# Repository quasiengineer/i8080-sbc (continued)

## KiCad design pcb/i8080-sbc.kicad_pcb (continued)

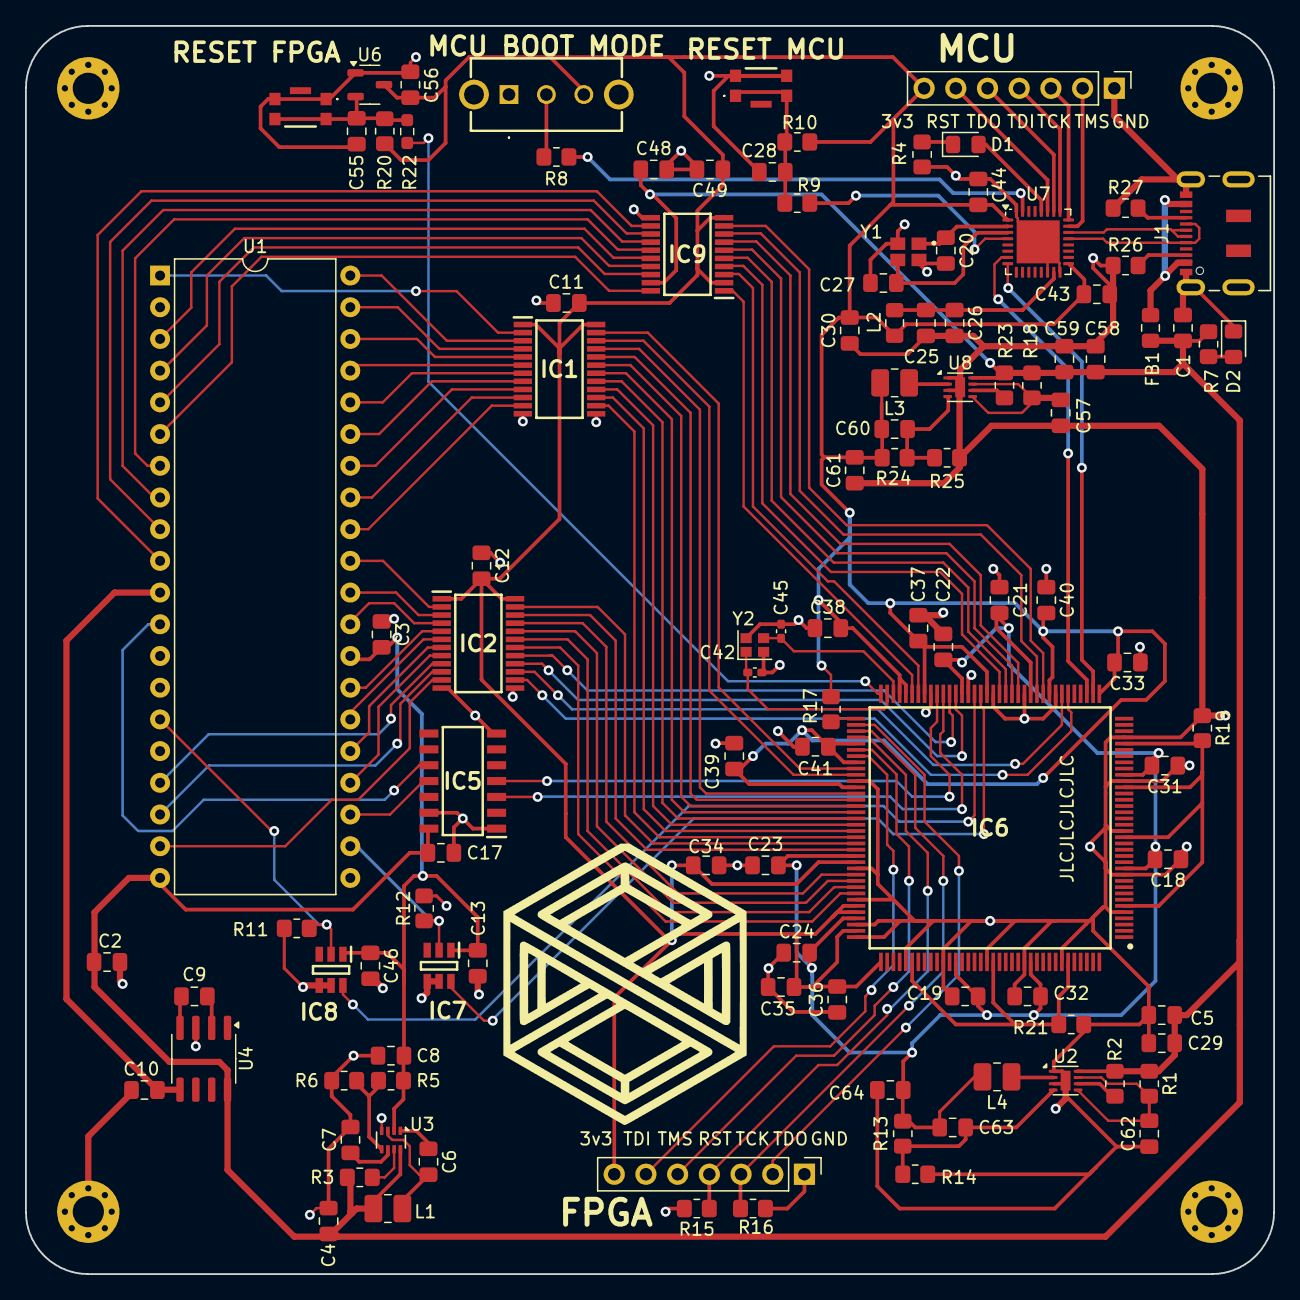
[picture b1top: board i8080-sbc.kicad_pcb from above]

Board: 2 copper layers, 100.0 x 100.0 mm, 115 parts (0 on the bottom side), 119 nets.

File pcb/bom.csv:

"Reference","Value","Footprint","Mouser Part Number","Qty"
"C1,C7,C25,C57,C62","1u","Capacitor_SMD:C_0805_2012Metric_Pad1.18x1.45mm_HandSolder","187-CL21B105KAFNNNG","5"
"C2,C3,C6,C11,C12,C13,C17,C18,C19,C21,C22,C23,C24,C26,C28,C29,C31,C32,C33,C34,C35,C36,C37,C38,C39,C40,C41,C43,C44,C46,C48,C49,C56,C58","100n","Capacitor_SMD:C_0805_2012Metric_Pad1.18x1.45mm_HandSolder","187-CL21B104KBCNNND","34"
"C4,C30","4u7,4u7, low-ESR","Capacitor_SMD:C_0805_2012Metric_Pad1.18x1.45mm_HandSolder","187-CL21A475KAQNNNE","2"
"C5,C59,C61,C64","22u","Capacitor_SMD:C_0805_2012Metric_Pad1.18x1.45mm_HandSolder","187-CL21A226MAYNNNE","4"
"C8,C9,C10,C55","10u,10u, low-ESR","Capacitor_SMD:C_0805_2012Metric_Pad1.18x1.45mm_HandSolder","187-CL21A106KAYNNNF","4"
"C20,C27","10p","Capacitor_SMD:C_0805_2012Metric_Pad1.18x1.45mm_HandSolder","710-885012007051","2"
"C42,C45","10p","Capacitor_SMD:C_0402_1005Metric_Pad0.74x0.62mm_HandSolder","603-CC402JRNPO8BN100","2"
"C60","33p","Capacitor_SMD:C_0805_2012Metric_Pad1.18x1.45mm_HandSolder","710-885012007031","1"
"C63","22p","Capacitor_SMD:C_0805_2012Metric_Pad1.18x1.45mm_HandSolder","710-885012007053","1"
"D1","Red","LED_SMD:LED_0805_2012Metric_Pad1.15x1.40mm_HandSolder","710-150080RS75000","1"
"D2","Green","LED_SMD:LED_0805_2012Metric_Pad1.15x1.40mm_HandSolder","710-150080GS75000","1"
"FB1","Ferrite_Bead","Inductor_SMD:L_0805_2012Metric_Pad1.15x1.40mm_HandSolder","652-MG2029-101Y","1"
"H1,H2,H3,H4","2.5mm","MountingHole:MountingHole_2.5mm_Pad_Via","","4"
"IC1,IC2","SN74LVC861APW","Project components:SOP65P640X120-24N","595-SN74LVC861APW","2"
"IC5","CD74HC243M96","Project components:SOIC127P600X175-14N","595-CD74HC243M96","1"
"IC6","M2GL005-TQG144I","Project components:QFP50P2200X2200X160-144N","494-M2GL005-TQG144I","1"
"IC7,IC8","UCC27511DBVR","SOT95P280X145-6N","595-UCC27511DBVR","2"
"IC9","TXS0108EPWRG4","Project components:SOP65P640X120-20N","595-TXS0108EPWRG4","1"
"J1","Type-C","Connector_USB:USB_C_Receptacle_JAE_DX07S016JA1R1500","656-DX07S016JA1R1500","1"
"J2,J4","FPGA JTAG,MCU JTAG","Connector_PinHeader_2.54mm:PinHeader_1x07_P2.54mm_Vertical","649-1012937990701BLF","2"
"L1","8u2, 800mA","Inductor_SMD:L_1008_2520Metric_Pad1.43x2.20mm_HandSolder","81-DFE252012F-8R2MP2","1"
"L2","27n","Inductor_SMD:L_0805_2012Metric_Pad1.15x1.40mm_HandSolder","652-CE201210-27NJ","1"
"L3,L4","0u68, 5.5A","Inductor_SMD:L_1008_2520Metric_Pad1.43x2.20mm_HandSolder","652-SRP2512-R68M","2"
"R1,R18","10","Resistor_SMD:R_0805_2012Metric_Pad1.20x1.40mm_HandSolder","603-RT0805DRE0710RL","2"
"R2,R13,R14,R23","100k","Resistor_SMD:R_0805_2012Metric_Pad1.20x1.40mm_HandSolder","603-RT0805DRE07100KL","4"
"R3,R6","30k","Resistor_SMD:R_0805_2012Metric_Pad1.20x1.40mm_HandSolder","603-RT0805DRE0730KL","2"
"R4","4k7","Resistor_SMD:R_0805_2012Metric_Pad1.20x1.40mm_HandSolder","603-RT0805FRE134K7L","1"
"R5","330k","Resistor_SMD:R_0805_2012Metric_Pad1.20x1.40mm_HandSolder","603-RT0805FRE07330KL","1"
"R7","2k2","Resistor_SMD:R_0805_2012Metric_Pad1.20x1.40mm_HandSolder","603-RT0805FRE072K2L","1"
"R8,R10,R19,R20,R21","10k","Resistor_SMD:R_0805_2012Metric_Pad1.20x1.40mm_HandSolder","603-RT0805DRD0710KL","5"
"R9,R11,R12","220","Resistor_SMD:R_0805_2012Metric_Pad1.20x1.40mm_HandSolder","603-RT0805FRE07220RL","3"
"R15,R16,R17","1k","Resistor_SMD:R_0805_2012Metric_Pad1.20x1.40mm_HandSolder","603-RT0805FRE071KL","3"
"R22","50","Resistor_SMD:R_0603_1608Metric_Pad0.98x0.95mm_HandSolder","603-RT0603BRE0750RL","1"
"R24","158k","Resistor_SMD:R_0805_2012Metric_Pad1.20x1.40mm_HandSolder","603-RT0805FRE07158KL","1"
"R25","34k8","Resistor_SMD:R_0805_2012Metric_Pad1.20x1.40mm_HandSolder","603-RT0805FRE0734K8L","1"
"R26,R27","5k1","Resistor_SMD:R_0805_2012Metric_Pad1.20x1.40mm_HandSolder","603-RT0805FRE075K1L","2"
"SW1","BOOT_MODE","Project components:SLW1215865AD","SLW-121586-5A-D","1"
"SW2,SW3","RESET_FPGA,RESET_MCU","Project components:435451019820","710-435451019820","2"
"U1","8080A","Package_DIP:DIP-40_W15.24mm","571-1-2199299-5","1"
"U2,U8","LX7167ACLD-TR","Package_DFN_QFN:DFN-8-1EP_2x2mm_P0.5mm_EP0.8x1.6mm","494-LX7167ACLD-TR","2"
"U3","MP3438","Package_TO_SOT_SMD:SOT-583-8","946-MP3438GTL-P","1"
"U4","ICL7660","Package_SO:SOIC-8_3.9x4.9mm_P1.27mm","968-ICL7660CBAZA-T","1"
"U6","APX803-31SAG-7","Package_TO_SOT_SMD:SOT-23-3","621-APX803-31SAG-7 ","1"
"U7","STM32G4A1KEUx","Package_DFN_QFN:QFN-32-1EP_5x5mm_P0.5mm_EP3.45x3.45mm","511-STM32G4A1KEU6","1"
"Y1","16Mhz, CL=10p","Project components:XTAL_ECS-160-10-36-CKM-TR3","520-160-10-36CKM-TR3","1"
"Y2","16Mhz","Crystal:Crystal_SMD_2016-4Pin_2.0x1.6mm","81-XRCGB16M000FXN02R","1"

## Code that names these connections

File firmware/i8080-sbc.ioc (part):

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Mcu.Name=STM32G4A1KEUx
Mcu.Package=UFQFPN32
Mcu.UserName=STM32G4A1KEUx
PA11.Mode=Device
PA11.Signal=USB_DM
PA12.Mode=Device
PA12.Signal=USB_DP
PA13.Mode=JTAG_5_pins
PA13.Signal=SYS_JTMS-SWDIO
PA14.Mode=JTAG_5_pins
PA14.Signal=SYS_JTCK-SWCLK
PA15.Mode=JTAG_5_pins
PA15.Signal=SYS_JTDI
PA2.Mode=Asynchronous
PA2.Signal=USART2_TX
PA3.Mode=Asynchronous
PA3.Signal=USART2_RX
PB3.Mode=JTAG_5_pins
PB3.Signal=SYS_JTDO-SWO
PB4.Mode=JTAG_5_pins
PB4.Signal=SYS_JTRST
PB5.GPIOParameters=GPIO_Label
PB5.GPIO_Label=LED_OUT
PB5.Signal=GPIO_Output
RCC.HSE_VALUE=8000000
RCC.SYSCLKFreq_VALUE=64000000
RCC.SYSCLKSource=RCC_SYSCLKSOURCE_PLLCLK
board=custom

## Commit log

2025-05-22 Initial
2025-05-22 BOM formatting
2025-05-24 fix silkscreen for MCU JTAG pins
